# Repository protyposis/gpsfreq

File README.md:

High-Precision Audio Drift Measurements with GPS
------------------------------------------------

This repo contains auxiliary material to the guide [High-Precision Audio Drift Measurements with GPS](http://protyposis.net/clockdrift/high-precision-audio-drift-measurements-with-gps/).

License
=======

All material in this repository is licensed under the Creative Commons Attribution-NonCommercial-ShareAlike 4.0 International License. To view a copy of this license, visit http://creativecommons.org/licenses/by-nc-sa/4.0/

Copyright © 2014, 2015 Mario Guggenberger <mg@protyposis.net>

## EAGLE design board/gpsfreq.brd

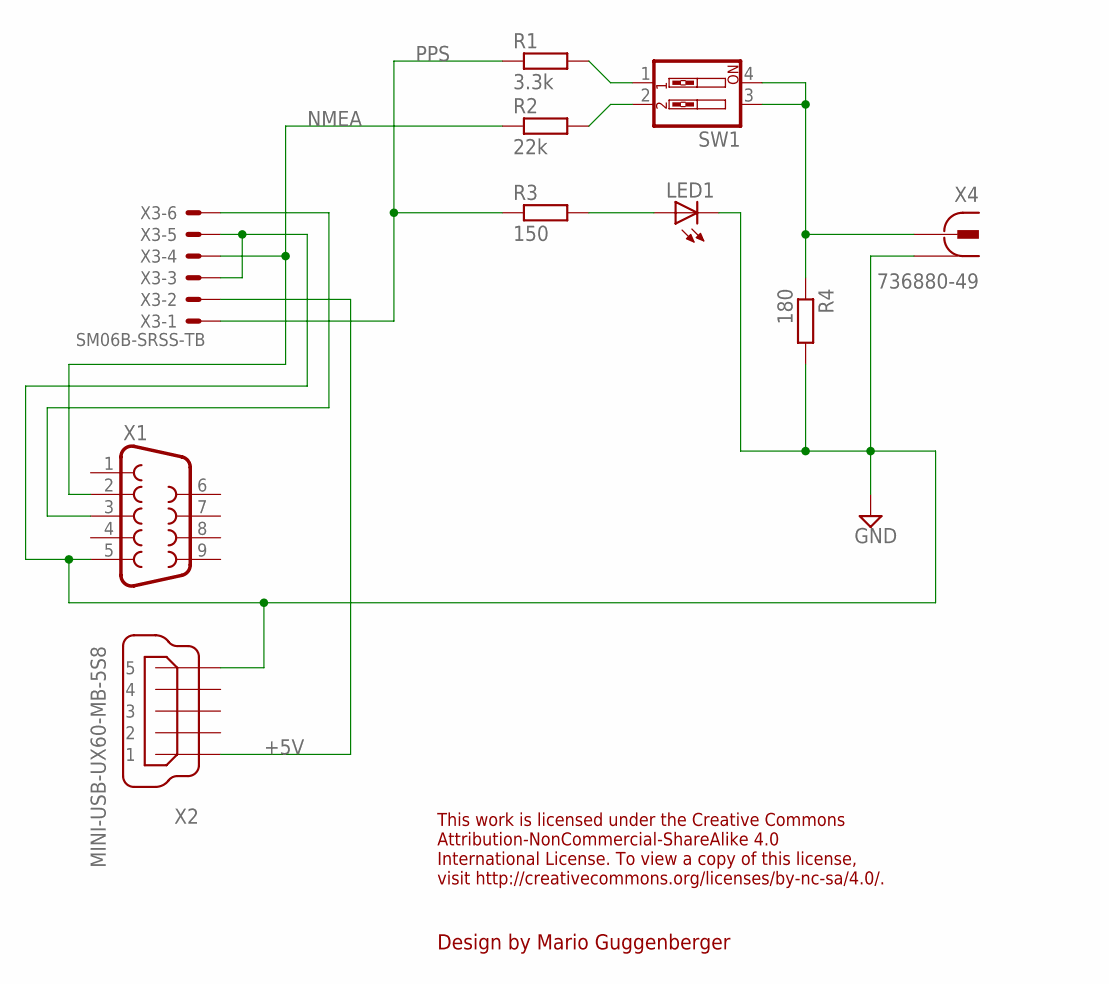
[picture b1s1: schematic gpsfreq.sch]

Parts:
LED1: LED3MM
R1: 3.3k; 0204/7
R2: 22k; 0204/7
R3: 150; 0204/7
R4: 180; 0204/7
SW1: SW_DIP-2; EDG-02
X1: F09H
X2: MINI-USB-UX60-MB-5S8; UX60-MB-5S8
X3: SM06B-SRSS-TB
X4: 736880-49

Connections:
+5V: X2.1, X3.2
GND: LED1.K (C), R4.2, X1.5, X2.5, X3.3, X3.5, X4.1, X4.1@1 (1), X4.1@2 (1)
unnamed: LED1.A, R3.2
unnamed: R4.1, SW1.3, SW1.4, X4.2
unnamed: R1.2, SW1.1
unnamed: R2.2, SW1.2
unnamed: X1.3, X3.6
NMEA: R2.1, X1.2, X3.4
PPS: R1.1, R3.1, X3.1

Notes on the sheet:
This work is licensed under the Creative Commons Attribution-NonCommercial-ShareAlike 4.0 International License. To view a copy of this license, visit http://creativecommons.org/licenses/by-nc-sa/4.0/.
Design by Mario Guggenberger

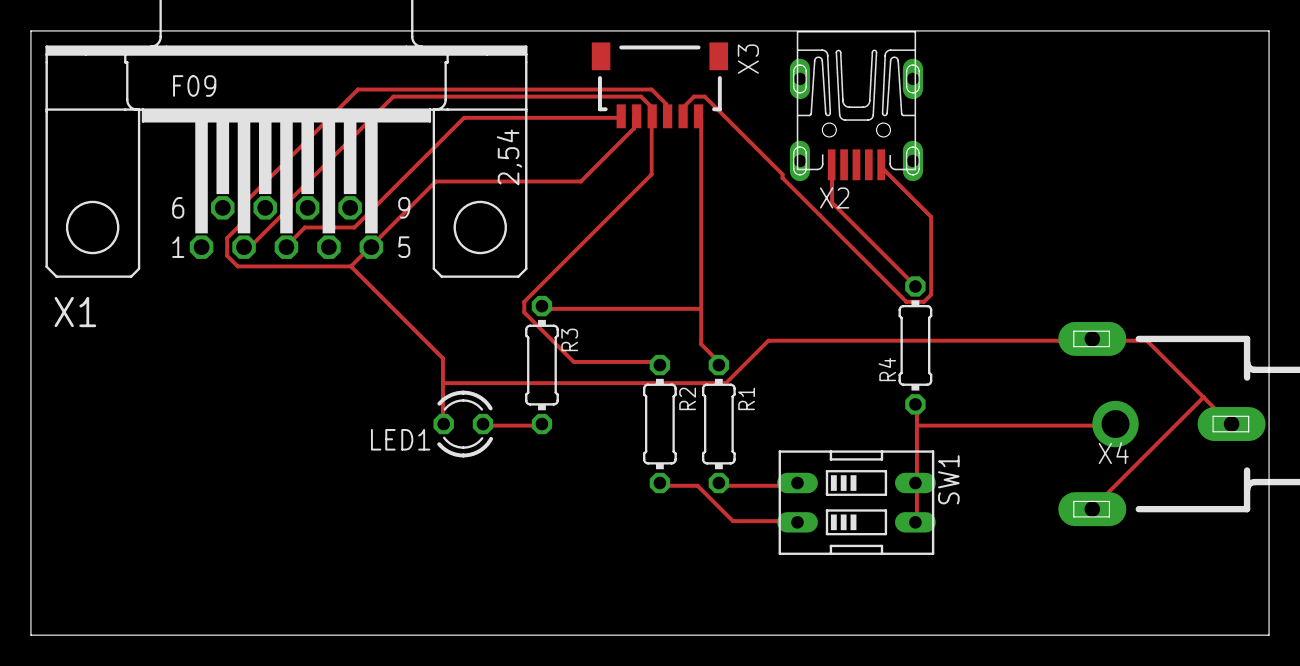
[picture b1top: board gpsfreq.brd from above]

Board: 2 copper layers, 80.0 x 39.0 mm, 11 parts (0 on the bottom side), 9 nets.

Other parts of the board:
U$1: A5L-LOC

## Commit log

2015-06-10 Add adapter board schematics
2015-06-10 Add matlab analysis script
2015-06-17 Add Spectrum Lab settings file
2015-08-19 Add Garmin GPS 18x LVC config file
2015-08-19 Move Spectrum Lab settings file to subfolder
2015-08-20 Add README.md
